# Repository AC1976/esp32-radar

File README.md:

# esp32-radar

A sweeping, radar-style display of nearby aircraft on an ESP32-C6 running MicroPython.
Live ADS-B positions come from the public [adsb.lol](https://api.adsb.lol) API (no key needed) and are
drawn as fading "phosphor" blips under a rotating beam.

## Hardware

- ESP32-C6 board
- 240x240 SPI TFT: GC9A01 (round, recommended) or ST7789 (square)
- Optional second display (same type): low aircraft on one screen, high on the other
- Optional: 10-LED WS2812 (NeoPixel) strip as an inbound-traffic proximity bar

## Wiring

Set `BOARD` at the top of `main.py` to match your board; the pin map follows automatically.

| Signal | Seeed XIAO ESP32C6 (`XIAO_C6`) | ESP32-C6-DevKitC-1 (`DEVKITC`) |
|---|---|---|
| Display VCC (3.3 V only!) | 3V3 | 3V3 |
| Display GND | GND | GND |
| Display SCL (SPI clock) | D10 · GPIO 18 | GPIO 6 |
| Display SDA (SPI MOSI) | D9 · GPIO 20 | GPIO 7 |
| Display RES | D4 · GPIO 22 | GPIO 18 |
| Display DC | D3 · GPIO 21 | GPIO 19 |
| Display CS | D2 · GPIO 2 | GPIO 20 |
| Display BLK | D1 · GPIO 1 | GPIO 21 |
| Display 2 CS (all other pins shared with display 1) | D8 · GPIO 19 | GPIO 23 |
| Strip 5V / GND | 5V / GND | 5V / GND |
| Strip DIN (via 330 ohm) | D0 · GPIO 0 | GPIO 22 |

Display 2 shares SCL, SDA, DC, RES, BLK, VCC and GND with display 1 and only needs its own CS wire.
Without a second display, remove the `tft2` lines in `main.py`.

Diagrams: [`esp32-radar-wiring-xiao.svg`](esp32-radar-wiring-xiao.svg) and
[`esp32-radar-wiring.svg`](esp32-radar-wiring.svg) (DevKitC).

XIAO notes: it ships without headers (solder them first); its 5V pin only carries USB power;
`main.py` drives GPIO3/GPIO14 low to enable the RF switch and select the on-board antenna.

## LED proximity bar

Once per sweep (as the beam passes north) the strip shows the closest aircraft, at any flight
level, that is inside the radar range (`RANGE_KM`), inside `LED_SECTOR` (default: bearing 0-90 deg,
the north-east quarter, drawn as two dim cyan lines on the radar) **and** closing on your position at
`MIN_CLOSING_KT` or more. The bar spans the radar range (10 LEDs = 1.5 km each at 15 km): one LED at
the outer edge, all ten overhead. It animates up or down and goes dark when nothing qualifies.
Colours run green (far), yellow, orange, red (overhead); brightness scales from `LED_BRIGHT_MIN`
with one LED to `LED_BRIGHT` with all ten lit.

Wiring: strip 5V to the board's 5V/VBUS pin (not 3V3), GND to GND, DIN to `LED_PIN` (GPIO 0 on the
XIAO). A 330 ohm resistor in the data line and a common ground are recommended.

## Software

- MicroPython v1.24 or newer for ESP32-C6
- A pure-Python display driver with `blit_buffer()`, e.g.
  [russhughes/gc9a01py](https://github.com/russhughes/gc9a01py) or
  [russhughes/st7789py_mpy](https://github.com/russhughes/st7789py_mpy)

## Setup

1. Flash MicroPython to the ESP32-C6.
2. Copy the display driver `.py` file to the board.
3. Copy `secrets.example.py` to `secrets.py` and fill in your Wi-Fi credentials
   (`secrets.py` is git-ignored).
4. Add your position to `secrets.py` (`HOME_LAT = ...`, `HOME_LON = ...`, decimal degrees) so it
   is not committed, and edit the config block at the top of `main.py` (range, sweep speed, altitude
   bands, LED sector, pins).
5. Copy both files to the board (`mpremote cp main.py secrets.py :`) and reset.

## How it works

Every frame is drawn with MicroPython's built-in `framebuf` module into a small RGB565 buffer,
one horizontal strip at a time (`STRIP_H` rows), and each strip is pushed to the display in one
SPI transfer. The afterglow is a fan of
filled triangles in decreasing brightness; each aircraft's brightness depends on how many
degrees ago the beam passed its bearing. A background thread polls the API every few seconds,
and positions are dead-reckoned from ground speed and track between updates.

## Notes

- Respect the API rate limit (max ~1 request/second).
- **Data source.** `api.airplanes.live` now returns HTTP 403 unless you contact them by email first,
  so `API_URL` points at adsb.lol, which serves the same JSON format. Change `API_URL` to switch.
- **Memory.** A full 240x240 RGB565 frame (115 KB) leaves too little RAM for Wi-Fi, TLS and the
  fetch thread on the C6, so `main.py` draws and sends the frame in strips that share one small
  buffer (28.8 KB). `STRIP_H` must divide 240 evenly.
- **SPI MISO pin.** The display never sends data back, but if no `miso` is given MicroPython uses the
  C6 default (GPIO 2), which is the display CS pin on the XIAO map, and the screen stays dark.
  `main.py` therefore passes a dummy `MISO_PIN` (GPIO 23).
- **Two displays.** Display A (CS D2) shows aircraft from `MIN_ALT_FT` (100 ft) to `SPLIT_FT` (5000 ft),
  display B (CS D8) everything above. The base layer (afterglow, grid, beam) is drawn once per strip and
  copied to the second buffer. Only display A gets the `reset` pin: the RES line is shared, and B's CS is
  held high while A initialises. With two 30-row strip buffers (`STRIP_H = 30`) memory matches the
  single-display build; two 60-row buffers ran out of memory (`ENOMEM` in the fetch thread).
  Positions are dead-reckoned between API calls (`FETCH_S` = 18 s).
- **Labels.** Each blip shows the airline ICAO code from the callsign and the aircraft type, with ground
  speed and flight level beneath (e.g. `KLM A21N` / `250 FL065`). They stay visible for `LABEL_DEG`
  degrees after the beam passes. `KLC` is KLM Cityhopper.

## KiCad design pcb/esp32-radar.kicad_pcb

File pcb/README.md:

# esp32-radar PCB (draft 1)

Carrier board for the dual-display radar: two GC9A01 round modules plug into 1x8 sockets, a XIAO ESP32-C6
plugs into two 1x7 sockets (USB-C to the right), and a 74AHCT125 (DIP-14, in a socket) level-shifts the
WS2812 data line to 5 V. The display modules lie flat on the board, pin row at the top edge, so the whole top half of the board is
covered by the two modules; everything else sits in the strip below them. Everything is through-hole.
Board is about 85 x 79 mm, 2 layers, GND pour both sides.

Regenerate with KiCad's Python (also writes the routing):

    /Applications/KiCad/KiCad.app/Contents/Frameworks/Python.framework/Versions/3.9/bin/python3 build_pcb.py

## Nets and pin map
| Net | XIAO pin | Where |
|---|---|---|
| SCL | D10 (GPIO18) | both displays |
| SDA | D9 (GPIO20) | both displays |
| DC | D3 (GPIO21) | both displays |
| RES | D4 (GPIO22) | both displays (shared) |
| BLK | D1 (GPIO1) | both displays |
| CS1 | D2 (GPIO2) | display A (low, below 5000 ft) |
| CS2 | D8 (GPIO19) | display B (high) |
| LED_IN | D0 (GPIO0) | 74AHCT125 pin 2 (10k pull-down) |
| +3V3 / GND / +5V | 3V3 / GND / 5V | power |

Socket order on each display header, left to right, same as the module silkscreen with the pin row at the top:
GND VCC SCL SDA RES DC CS BLK.

## Parts
- 2x 1x8 female header 2.54 mm (displays), 2x 1x7 female header 2.54 mm (XIAO)
- 74AHCT125 in a DIP-14 socket (gate 1 used, unused gates grounded)
- R1 330 ohm (data line), R2 10 kohm (pull-down), both 1/4 W axial
- C1, C2, C3 100 nF ceramic (2.5 mm pitch), C4 10 uF ceramic (5 mm pitch)
- C5 1000 uF electrolytic 10 mm, mounted on the BACK (optional)
- J5 3-way screw terminal 5.08 mm: 5V, GND, DIN (LED strip)
- 4x M2.5 mounting holes (corners; two are optional, see notes)

## Mechanical notes
- Display modules (36 x 44 mm, glass 32.4 mm, pin row 21.5 mm above the glass centre) are drawn on the
  Dwgs.User layer. They sit directly above the board; nothing tall is placed under them (only copper).
- Display centres are 40.64 mm apart.
- The XIAO antenna end (left, opposite USB-C) has a copper keep-out. Keep metal away from it.
- Check before ordering: pin order and pitch against a real module, hole positions against the case, and the
  height of the sockets versus the case depth.

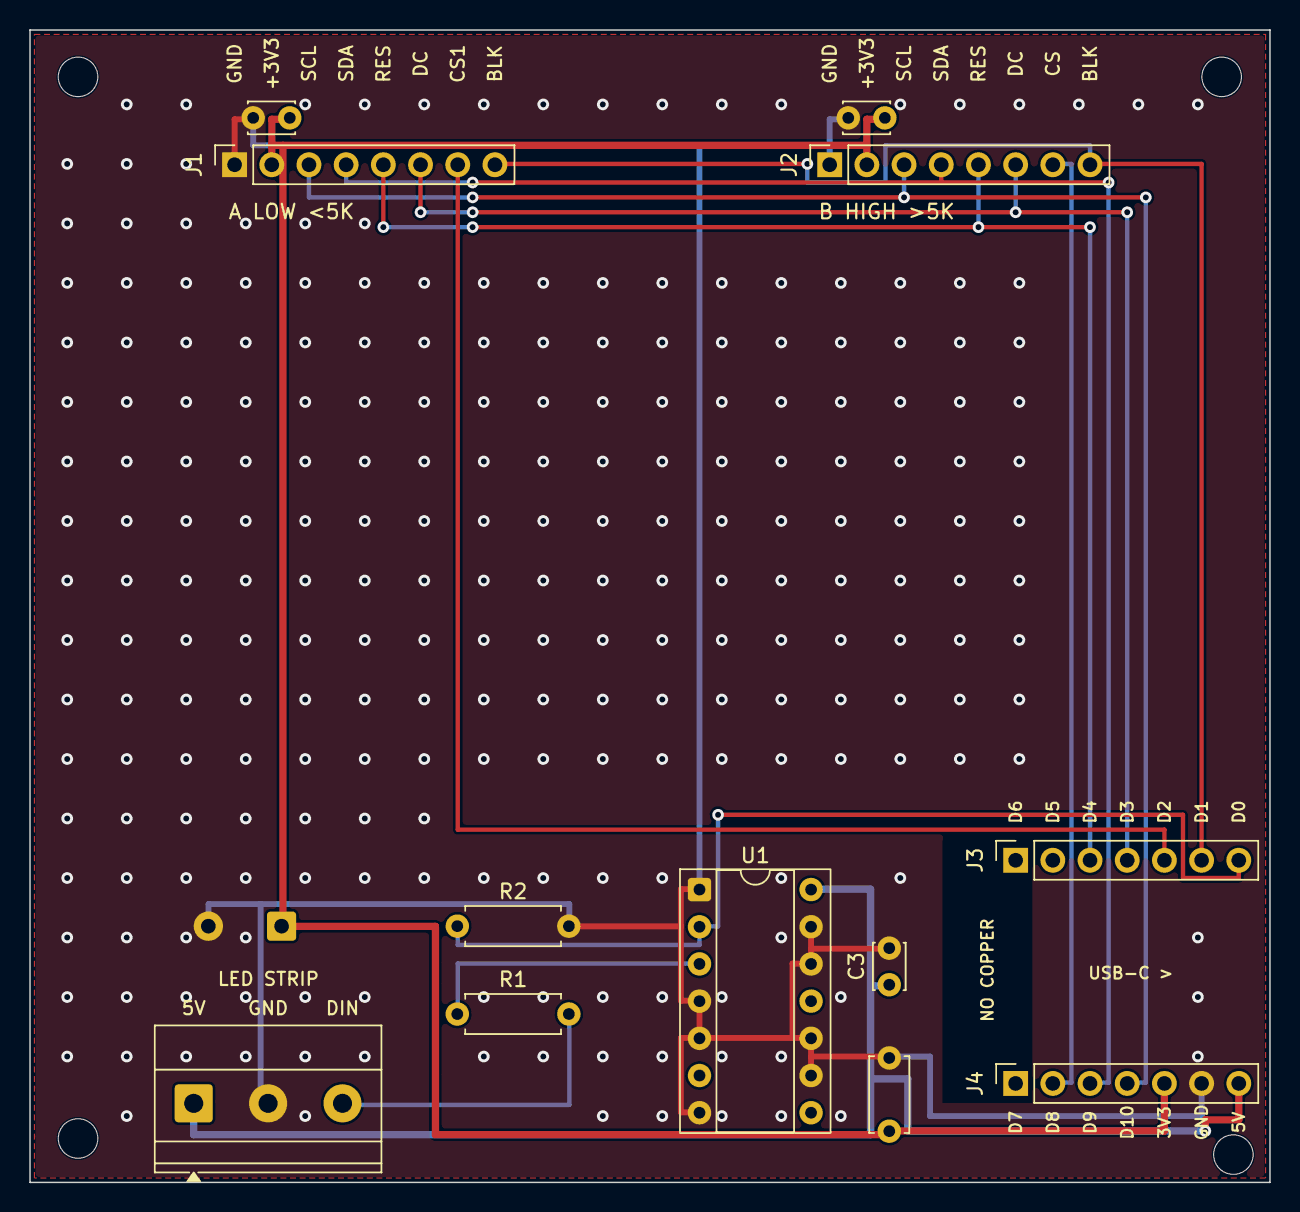
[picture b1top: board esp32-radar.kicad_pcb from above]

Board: 2 copper layers, 84.7 x 78.7 mm, 17 parts (1 on the bottom side), 13 nets.

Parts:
C1: 100nF (display A); C_Disc_D3.0mm_W2.0mm_P2.50mm
C2: 100nF (display B); C_Disc_D3.0mm_W2.0mm_P2.50mm
C3: 100nF (74AHCT125); C_Disc_D3.0mm_W2.0mm_P2.50mm
C4: 10uF ceramic (3V3); C_Disc_D5.0mm_W2.5mm_P5.00mm
C5: 1000uF (optional, back); CP_Radial_D10.0mm_P5.00mm
H1, H2, H3, H4: MountingHole_2.7mm_M2.5
J1: DISPLAY A (LOW) 1x08 socket; PinSocket_1x08_P2.54mm_Vertical
J2: DISPLAY B (HIGH) 1x08 socket; PinSocket_1x08_P2.54mm_Vertical
J3: XIAO top row (D6..D0); PinSocket_1x07_P2.54mm_Vertical
J4: XIAO bottom row (D7..5V); PinSocket_1x07_P2.54mm_Vertical
J5: LED strip: 5V GND DIN; TerminalBlock_Phoenix_MKDS-1,5-3-5.08_1x03_P5.08mm_Horizont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
R1: 330R (data line); R_Axial_DIN0207_L6.3mm_D2.5mm_P7.62mm_Horizontal
R2: 10k (pull-down); R_Axial_DIN0207_L6.3mm_D2.5mm_P7.62mm_Horizontal
U1: 74AHCT125 (DIP-14); DIP-14_W7.62mm_Socket

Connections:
+3V3: C1.2, C2.2, C4.1, C5.1, J1.2, J2.2, J4.5
+5V: C3.1, J4.7, J5.1, U1.14
BLK: J1.8, J2.8, J3.6
CS1: J1.7, J3.5
CS2: J2.7, J4.2
DC: J1.6, J2.6, J3.4
DIN: J5.3, R1.2
GND: C1.1, C2.1, C3.2, C4.2, C5.2, J1.1, J2.1, J4.6, J5.2, R2.2, U1.1, U1.4, U1.5, U1.7, U1.9, U1.10, U1.12, U1.13
LED_5V: R1.1, U1.3
LED_IN: J3.7, R2.1, U1.2
RES: J1.5, J2.5, J3.3
SCL: J1.3, J2.3, J4.4
SDA: J1.4, J2.4, J4.3

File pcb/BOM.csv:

Qty,References,What to buy,Notes
1,C1,"Capacitor 100 nF (0.1 uF) ceramic X7R, radial, 2.54 mm lead pitch, 50 V",No polarity.
1,C2,"Capacitor 100 nF (0.1 uF) ceramic X7R, radial, 2.54 mm lead pitch, 50 V",No polarity.
1,C3,"Capacitor 100 nF (0.1 uF) ceramic X7R, radial, 2.54 mm lead pitch, 50 V",No polarity.
1,C4,"Capacitor 10 uF ceramic X7R, radial, 5.08 mm lead pitch, 16 V",No polarity. A 10 uF electrolytic also works: then + goes to pad 1 (the +3V3 pad).
1,C5,"Capacitor 1000 uF electrolytic, radial, 10 mm diameter, 5 mm lead pitch, 10 V or 16 V","Optional. POLARISED: + to pad 1 (the square pad, +3V3). Mounted on the back of the board."
4,H1 H2 H3 H4,M2.5 screw + standoff (optional),Four corner holes; only if the case uses them.
1,J1,"1x8 female header, 2.54 mm",Display A socket. Pins must be long enough to take the module's pins.
1,J2,"1x8 female header, 2.54 mm",Display B socket.
1,J3,"1x7 female header, 2.54 mm",XIAO socket. The XIAO ships without headers: it needs 2x 1x7 MALE pins soldered on.
1,J4,"1x7 female header, 2.54 mm",XIAO socket (second row).
1,J5,"Screw terminal 3-way, 5.08 mm pitch, wire entry on the side","e.g. Phoenix MKDS 1,5/3-5,08 or a generic KF128-5.08 clone. Wire entry faces the board edge."
1,R1,"Resistor 330 ohm 1/4 W, axial",In series with the LED data line.
1,R2,"Resistor 10 kohm 1/4 W, axial",Holds the LED data input low while the XIAO boots.
1,U1,"DIP-14 IC socket, 7.62 mm row spacing",For the SN74AHCT125N you already have.
1,(U1 chip),"SN74AHCT125N, DIP-14",You have it. Goes in the DIP-14 socket.
1,(XIAO),Seeed XIAO ESP32-C6,You have it.
2,(displays),"GC9A01 1.28 in round display module, 8-pin",You have them.
